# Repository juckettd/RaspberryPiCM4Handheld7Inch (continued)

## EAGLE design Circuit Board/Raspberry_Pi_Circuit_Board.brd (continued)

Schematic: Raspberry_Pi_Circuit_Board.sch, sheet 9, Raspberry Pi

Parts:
RPI_PINS1-100, RPI_PINS101-200: CONN-DF40_CL0594-5437-8-00_2D

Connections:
BITCLK_IN: RPI_PINS1-100.49; also elsewhere on the board
BT_REG_ON: RPI_PINS1-100.34; also elsewhere on the board
BT_UART_CTS: RPI_PINS1-100.29; also elsewhere on the board
BT_UART_RTS: RPI_PINS1-100.50; also elsewhere on the board
BT_UART_RXD: RPI_PINS1-100.51; also elsewhere on the board
BT_UART_TXD: RPI_PINS1-100.55; also elsewhere on the board
DATA_IN: RPI_PINS1-100.25; also elsewhere on the board
DSI1_C_N: RPI_PINS101-200.87; also elsewhere on the board
DSI1_C_P: RPI_PINS101-200.89; also elsewhere on the board
DSI1_D0_N: RPI_PINS101-200.75; also elsewhere on the board
DSI1_D0_P: RPI_PINS101-200.77; also elsewhere on the board
DSI1_D1_N: RPI_PINS101-200.81; also elsewhere on the board
DSI1_D1_P: RPI_PINS101-200.83; also elsewhere on the board
ETH0_N: RPI_PINS1-100.10; also elsewhere on the board
ETH0_P: RPI_PINS1-100.12; also elsewhere on the board
ETH1_N: RPI_PINS1-100.6; also elsewhere on the board
ETH1_P: RPI_PINS1-100.4; also elsewhere on the board
ETH2_N: RPI_PINS1-100.9; also elsewhere on the board
ETH2_P: RPI_PINS1-100.11; also elsewhere on the board
ETH3_N: RPI_PINS1-100.5; also elsewhere on the board
ETH3_P: RPI_PINS1-100.3; also elsewhere on the board
ETH_LEDG: RPI_PINS1-100.15; also elsewhere on the board
ETH_LEDY: RPI_PINS1-100.17; also elsewhere on the board
GLOBAL_EN: RPI_PINS1-100.99; also elsewhere on the board
GND: RPI_PINS1-100.1, RPI_PINS1-100.2, RPI_PINS1-100.7, RPI_PINS1-100.8, RPI_PINS1-100.13, RPI_PINS1-100.14, RPI_PINS1-100.22, RPI_PINS1-100.23, RPI_PINS1-100.32, RPI_PINS1-100.33, RPI_PINS1-100.42, RPI_PINS1-100.43, RPI_PINS1-100.52, RPI_PINS1-100.53, RPI_PINS1-100.59, RPI_PINS1-100.60, RPI_PINS1-100.65, RPI_PINS1-100.66, RPI_PINS1-100.71, RPI_PINS1-100.74, RPI_PINS1-100.98, RPI_PINS101-200.7, RPI_PINS101-200.8, RPI_PINS101-200.13, RPI_PINS101-200.14, RPI_PINS101-200.19, RPI_PINS101-200.20, RPI_PINS101-200.25, RPI_PINS101-200.26, RPI_PINS101-200.31, RPI_PINS101-200.32, RPI_PINS101-200.37, RPI_PINS101-200.38, RPI_PINS101-200.44, RPI_PINS101-200.50, RPI_PINS101-200.55, RPI_PINS101-200.56, RPI_PINS101-200.61, RPI_PINS101-200.62, RPI_PINS101-200.67, RPI_PINS101-200.68, RPI_PINS101-200.73, RPI_PINS101-200.74, RPI_PINS101-200.79, RPI_PINS101-200.80, RPI_PINS101-200.85, RPI_PINS101-200.86, RPI_PINS101-200.91, RPI_PINS101-200.92, RPI_PINS101-200.97, RPI_PINS101-200.98; also elsewhere on the board
GPIO7: RPI_PINS1-100.37; also elsewhere on the board
GPIO8: RPI_PINS1-100.39; also elsewhere on the board
GPIO9: RPI_PINS1-100.40; also elsewhere on the board
GPIO10: RPI_PINS1-100.44; also elsewhere on the board
GPIO11: RPI_PINS1-100.38; also elsewhere on the board
GPIO12: RPI_PINS1-100.31; also elsewhere on the board
HDMI0_CEC: RPI_PINS101-200.51; also elsewhere on the board
HDMI0_CK_N: RPI_PINS101-200.90; also elsewhere on the board
HDMI0_CK_P: RPI_PINS101-200.88; also elsewhere on the board
HDMI0_D0_N: RPI_PINS101-200.84; also elsewhere on the board
HDMI0_D0_P: RPI_PINS101-200.82; also elsewhere on the board
HDMI0_D1_N: RPI_PINS101-200.78; also elsewhere on the board
HDMI0_D1_P: RPI_PINS101-200.76; also elsewhere on the board
HDMI0_D2_N: RPI_PINS101-200.72; also elsewhere on the board
HDMI0_D2_P: RPI_PINS101-200.70; also elsewhere on the board
HDMI0_HOTPLUG: RPI_PINS101-200.53; also elsewhere on the board
HDMI0_SCL: RPI_PINS101-200.100; also elsewhere on the board
HDMI0_SDA: RPI_PINS101-200.99; also elsewhere on the board
NPWR_LED: RPI_PINS1-100.95; also elsewhere on the board
N_EXTRST: RPI_PINS1-100.100; also elsewhere on the board
N_RPIBOOT: RPI_PINS1-100.93; also elsewhere on the board
RP1.8: RPI_PINS1-100.78, RPI_PINS1-100.88, RPI_PINS1-100.90
RP3.3: RPI_PINS1-100.84, RPI_PINS1-100.86; also elsewhere on the board
RUN_PG: RPI_PINS1-100.92; also elsewhere on the board
SCL0: RPI_PINS1-100.80; also elsewhere on the board
SCL1: RPI_PINS1-100.56; also elsewhere on the board
SDA0: RPI_PINS1-100.82; also elsewhere on the board
SDA1: RPI_PINS1-100.58; also elsewhere on the board
SDIO_CLK: RPI_PINS1-100.46; also elsewhere on the board
SDIO_CMD: RPI_PINS1-100.47; also elsewhere on the board
SDIO_DATA0: RPI_PINS1-100.45; also elsewhere on the board
SDIO_DATA1: RPI_PINS1-100.41; also elsewhere on the board
SDIO_DATA2: RPI_PINS1-100.24; also elsewhere on the board
SDIO_DATA3: RPI_PINS1-100.48; also elsewhere on the board
SD_CLK: RPI_PINS1-100.57; also elsewhere on the board
SD_CMD: RPI_PINS1-100.62; also elsewhere on the board
SD_DAT0: RPI_PINS1-100.63; also elsewhere on the board
SD_DAT1: RPI_PINS1-100.67; also elsewhere on the board
SD_DAT2: RPI_PINS1-100.69; also elsewhere on the board
SD_DAT3: RPI_PINS1-100.61; also elsewhere on the board
SD_PWR_ON: RPI_PINS1-100.75; also elsewhere on the board
USB2_N: RPI_PINS101-200.3; also elsewhere on the board
USB2_P: RPI_PINS101-200.5; also elsewhere on the board
USBOTG: RPI_PINS101-200.1; also elsewhere on the board
VREF5.0: RPI_PINS1-100.77, RPI_PINS1-100.79, RPI_PINS1-100.81, RPI_PINS1-100.83, RPI_PINS1-100.85, RPI_PINS1-100.87; also elsewhere on the board
WL_REG_ON: RPI_PINS1-100.30; also elsewhere on the board
WORDSEL_IN: RPI_PINS1-100.26; also elsewhere on the board

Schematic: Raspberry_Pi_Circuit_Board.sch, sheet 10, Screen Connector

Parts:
LCD_CONN: FPC-1-84952-5

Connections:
DSI1_C_N: LCD_CONN.11; also elsewhere on the board
DSI1_C_P: LCD_CONN.10; also elsewhere on the board
DSI1_D0_N: LCD_CONN.8; also elsewhere on the board
DSI1_D0_P: LCD_CONN.7; also elsewhere on the board
DSI1_D1_N: LCD_CONN.14; also elsewhere on the board
DSI1_D1_P: LCD_CONN.13; also elsewhere on the board
GND: LCD_CONN.3, LCD_CONN.6, LCD_CONN.9, LCD_CONN.12, LCD_CONN.15, LCD_CONN.MP_1 (MP), LCD_CONN.MP_2 (MP); also elsewhere on the board
SCL0: LCD_CONN.5; also elsewhere on the board
SDA0: LCD_CONN.4; also elsewhere on the board
VREF3.3: LCD_CONN.1, LCD_CONN.2; also elsewhere on the board

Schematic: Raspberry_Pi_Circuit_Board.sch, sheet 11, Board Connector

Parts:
BOARD_CONN_1: MEZZANINE-AXT630124

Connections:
AGND: BOARD_CONN_1.11; also elsewhere on the board
AUDSD: BOARD_CONN_1.14; also elsewhere on the board
D+1: BOARD_CONN_1.10; also elsewhere on the board
D+2: BOARD_CONN_1.8; also elsewhere on the board
D-1: BOARD_CONN_1.9; also elsewhere on the board
D-2: BOARD_CONN_1.7; also elsewhere on the board
ETH0_N: BOARD_CONN_1.22; also elsewhere on the board
ETH0_P: BOARD_CONN_1.23; also elsewhere on the board
ETH1_N: BOARD_CONN_1.20; also elsewhere on the board
ETH1_P: BOARD_CONN_1.21; also elsewhere on the board
ETH2_N: BOARD_CONN_1.18; also elsewhere on the board
ETH2_P: BOARD_CONN_1.19; also elsewhere on the board
ETH3_N: BOARD_CONN_1.16; also elsewhere on the board
ETH3_P: BOARD_CONN_1.17; also elsewhere on the board
ETH_LEDG: BOARD_CONN_1.24; also elsewhere on the board
ETH_LEDY: BOARD_CONN_1.25; also elsewhere on the board
GND: BOARD_CONN_1.15, BOARD_CONN_1.26, BOARD_CONN_1.27, BOARD_CONN_1.28, BOARD_CONN_1.29, BOARD_CONN_1.30, BOARD_CONN_1.MP_1 (MP), BOARD_CONN_1.MP_2 (MP), BOARD_CONN_1.MP_3 (MP), BOARD_CONN_1.MP_4 (MP); also elsewhere on the board
OUTL: BOARD_CONN_1.12; also elsewhere on the board
OUTR: BOARD_CONN_1.13; also elsewhere on the board
VBUS1: BOARD_CONN_1.2, BOARD_CONN_1.3, BOARD_CONN_1.4, BOARD_CONN_1.5, BOARD_CONN_1.6; also elsewhere on the board
VREF3.3: BOARD_CONN_1.1; also elsewhere on the board

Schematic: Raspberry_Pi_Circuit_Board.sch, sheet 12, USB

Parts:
C1: 100uF; CAP-603
C18, C19, C20, C21: 10uF; CAP-603
C42, C43: 0.1uF; CAP-603
C52, C53: 27pF; CAP-603
CLK_24M: CLK-ECS-240
R23, R24: 2.2K; RES-603
R27: 12K; RES-603
R28: 15K; RES-603
R30, R31, R32, R33: 36K; RES-603
RPI_BOOT_SW: DIP-A6TN-1104
TP14, TP15: TESTPOINT
USB_CURLIM: CURLIM-AP22653W6
USB_HUB: USBPORT-USB2514BT-I/M2
USB_IN: USB-USB3131-30-0230-A
USB_POE: POE_PROT-TPD4EUSB30DQAR
USB_SWI: USB_SWITCH-FSUSB42-D

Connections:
D+1: USB_HUB.4; also elsewhere on the board
D+2: USB_HUB.7; also elsewhere on the board
D-1: USB_HUB.3; also elsewhere on the board
D-2: USB_HUB.6; also elsewhere on the board
GND: C1.A, C18.A, C19.A, C20.A, C21.A, C42.A, C43.A, C52.A, C53.A, CLK_24M.GND_1 (GND), CLK_24M.GND_2 (GND), R24.C, R27.C, R28.A, R30.C, R31.C, R32.C, R33.C, RPI_BOOT_SW.2, USB_CURLIM.GND, USB_HUB.37, USB_IN.GND, USB_IN.MP_1 (MP), USB_IN.MP_2 (MP), USB_POE.GND_1 (GND), USB_POE.GND_2 (GND), USB_SWI./OE, USB_SWI.GND; also elsewhere on the board
unnamed: R32.A, USB_HUB.28
unnamed: R28.C, USB_CURLIM.ILIM
unnamed: R31.A, USB_HUB.22
unnamed: R30.A, USB_HUB.24
unnamed: R23.A, TP15.TP, USB_IN.VBUS
unnamed: C53.C, CLK_24M.OUT/IN, USB_HUB.32
unnamed: C52.C, CLK_24M.IN/OUT, USB_HUB.33
unnamed: R33.A, USB_HUB.25
unnamed: R27.A, USB_HUB.35
N_EXTRST: USB_HUB.26; also elsewhere on the board
N_OCS1: USB_CURLIM.NFAULT, USB_HUB.13, USB_HUB.17, USB_HUB.19, USB_HUB.21
N_RPIBOOT: RPI_BOOT_SW.1; also elsewhere on the board
PWR1: USB_CURLIM.EN, USB_HUB.12
TD+: USB_HUB.2; also elsewhere on the board
TD-: USB_HUB.1; also elsewhere on the board
USB2_N: USB_SWI.D-; also elsewhere on the board
USB2_P: USB_SWI.D+; also elsewhere on the board
USBD_N: USB_IN.D+, USB_POE.D2+, USB_SWI.HSD2+
USBD_P: USB_IN.D-, USB_POE.D2-, USB_SWI.HSD2-
USBH_N: USB_HUB.30, USB_SWI.HSD1-
USBH_P: USB_HUB.31, USB_SWI.HSD1+
USBOTG: R23.C, R24.A, USB_SWI.SEL; also elsewhere on the board
VBUS1: C1.C, C21.C, TP14.TP, USB_CURLIM.OUT; also elsewhere on the board
VREF3.3: C18.C, C19.C, C42.C, C43.C, USB_HUB.5, USB_HUB.10, USB_HUB.15, USB_HUB.23, USB_HUB.27, USB_HUB.29, USB_HUB.36, USB_SWI.VCC; also elsewhere on the board
VREF5.0: C20.C, USB_CURLIM.IN; also elsewhere on the board

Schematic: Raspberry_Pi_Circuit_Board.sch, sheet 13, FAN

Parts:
C44: 0.1uF; CAP-603
D3: DIODE-X3-WLB1608-2
FAN_CONN: CONN-282834-2
R19: 10K; RES-603
TP16: TESTPOINT
TR3: TRAN-DMG2302UKQ

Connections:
GND: C44.A, R19.A, TR3.S; also elsewhere on the board
GPIO12: R19.C, TP16.TP, TR3.G; also elsewhere on the board
unnamed: D3.A, FAN_CONN.2, TR3.D
VREF3.3: C44.C, D3.C, FAN_CONN.1; also elsewhere on the board

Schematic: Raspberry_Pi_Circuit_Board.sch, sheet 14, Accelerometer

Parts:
ACCEL: MMA8451; MMA845X_QFN_16MM
C45: 0.1uF; CAP-603
R20: 10K; RES-603

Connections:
GND: ACCEL.5 (GND), ACCEL.10 (GND), ACCEL.12 (GND), C45.A; also elsewhere on the board
unnamed: ACCEL.2 (BYP), C45.C
SA0: ACCEL.7 (SA0), R20.A
SCL1: ACCEL.4 (SCL); also elsewhere on the board
SDA1: ACCEL.6 (SDA); also elsewhere on the board
VREF3.3: ACCEL.1 (VDDIO), ACCEL.14 (VDD), R20.C; also elsewhere on the board

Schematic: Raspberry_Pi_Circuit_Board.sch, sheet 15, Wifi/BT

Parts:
C61, C62: 0.1uF; CAP-603
C63, C64: 10uF; CAP-603
CLK-32.768: CLK-ECS-327
WIFI/BT: IC-LWB5+

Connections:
BT_REG_ON: WIFI/BT.32; also elsewhere on the board
BT_UART_CTS: WIFI/BT.46; also elsewhere on the board
BT_UART_RTS: WIFI/BT.44; also elsewhere on the board
BT_UART_RXD: WIFI/BT.43; also elsewhere on the board
BT_UART_TXD: WIFI/BT.45; also elsewhere on the board
GND: C61.A, C62.A, C63.A, C64.A, CLK-32.768.GND, WIFI/BT.1, WIFI/BT.8, WIFI/BT.14, WIFI/BT.16, WIFI/BT.27, WIFI/BT.28, WIFI/BT.29, WIFI/BT.35, WIFI/BT.42, WIFI/BT.48, WIFI/BT.49, WIFI/BT.51, WIFI/BT.G1 (GND), WIFI/BT.G2 (GND), WIFI/BT.G3 (GND), WIFI/BT.G4 (GND), WIFI/BT.G5 (GND), WIFI/BT.G6 (GND), WIFI/BT.G7 (GND), WIFI/BT.G8 (GND), WIFI/BT.G9 (GND), WIFI/BT.G10 (GND), WIFI/BT.G11 (GND), WIFI/BT.G12 (GND), WIFI/BT.G13 (GND), WIFI/BT.G14 (GND), WIFI/BT.G15 (GND), WIFI/BT.G16 (GND), WIFI/BT.G17 (GND); also elsewhere on the board
SDIO_CLK: WIFI/BT.15; also elsewhere on the board
SDIO_CMD: WIFI/BT.12; also elsewhere on the board
SDIO_DATA0: WIFI/BT.9; also elsewhere on the board
SDIO_DATA1: WIFI/BT.10; also elsewhere on the board
SDIO_DATA2: WIFI/BT.13; also elsewhere on the board
SDIO_DATA3: WIFI/BT.11; also elsewhere on the board
SUSCLK: CLK-32.768.OUT, WIFI/BT.34
VREF1.8: C61.C, C63.C, CLK-32.768.OE, CLK-32.768.VDD, WIFI/BT.4, WIFI/BT.5, WIFI/BT.30; also elsewhere on the board
VREF3.3: C62.C, C64.C, WIFI/BT.7, WIFI/BT.17, WIFI/BT.18; also elsewhere on the board
WL_REG_ON: WIFI/BT.33; also elsewhere on the board

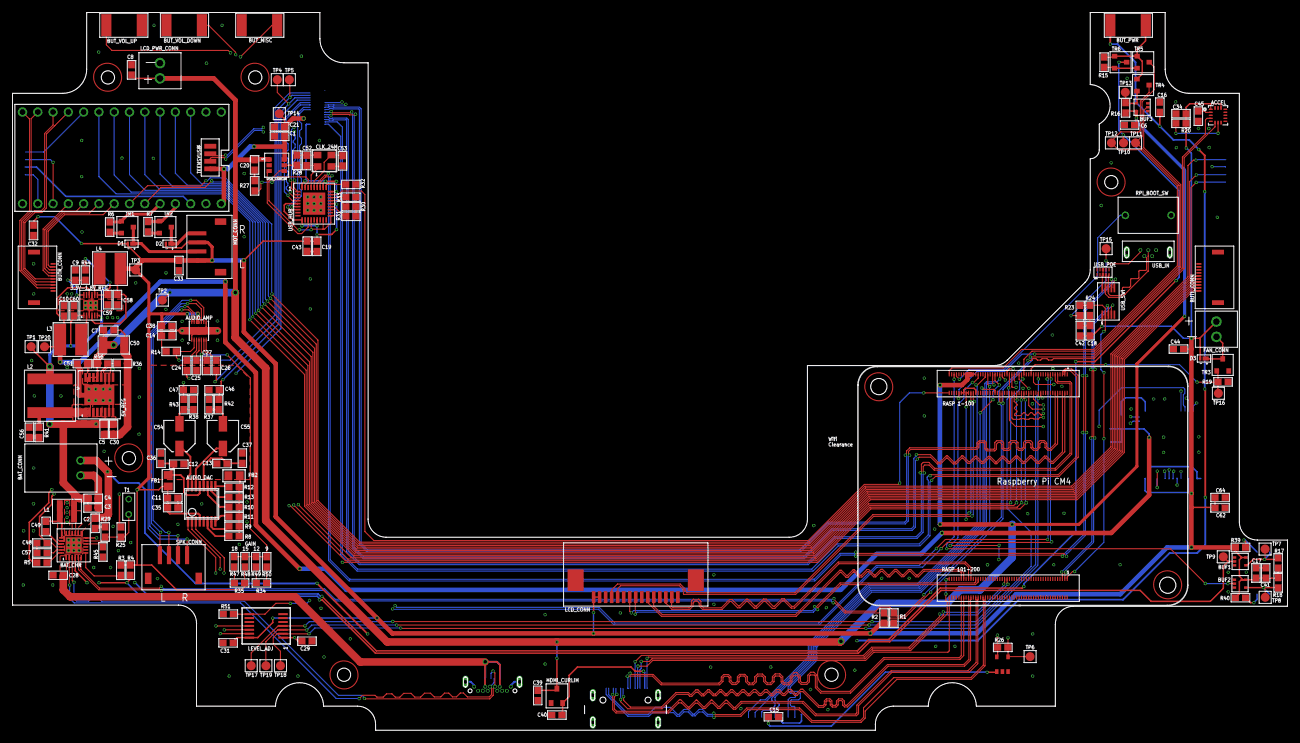
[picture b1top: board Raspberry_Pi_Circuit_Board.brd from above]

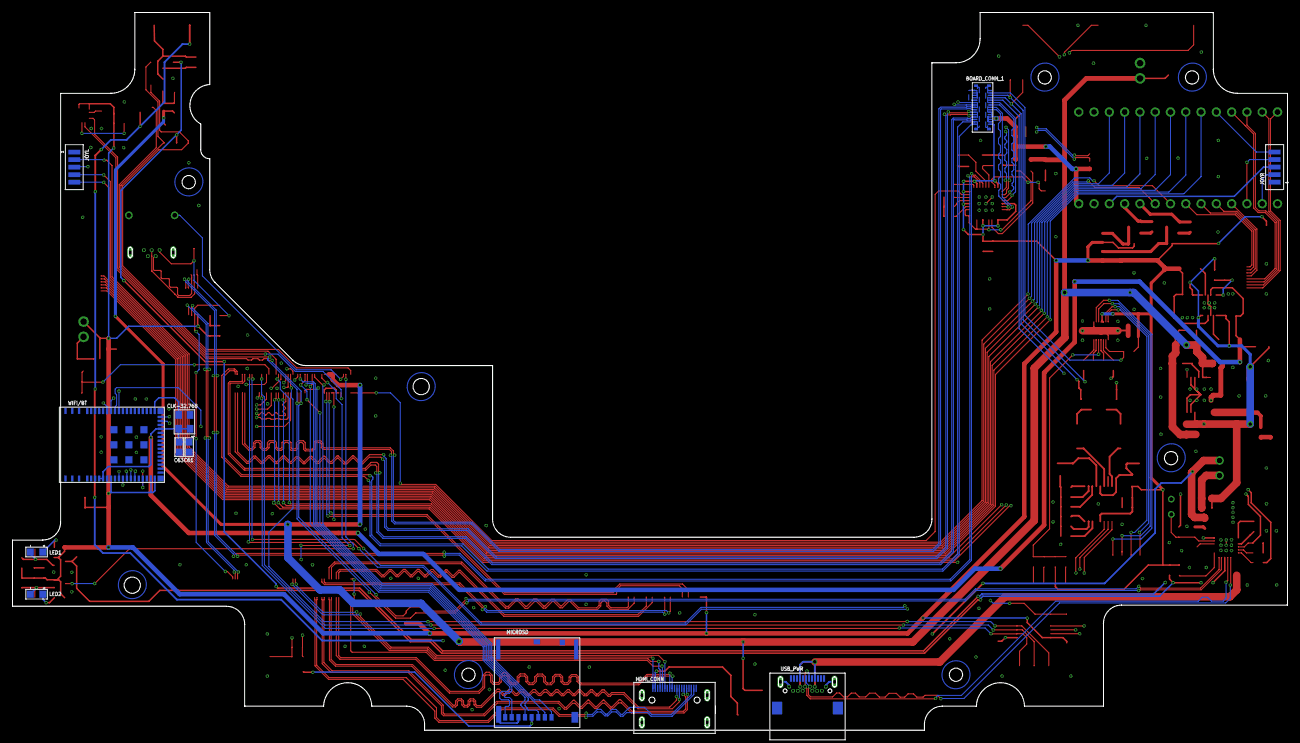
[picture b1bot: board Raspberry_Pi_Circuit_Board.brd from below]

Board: 4 copper layers, 211.9 x 119.3 mm, 192 parts (12 on the bottom side), 184 nets.

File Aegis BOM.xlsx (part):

Item | Component | Qty | Price | Total | Link
Power Items
Battery Charging IC | BAT_CHR | 1 | 3.76 | 3.76 | https://www.digikey.com/product-detail/en/texas-instruments/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
5V Boost IC | 5V_REG | 1 | 2.68 | 2.68 | https://www.digikey.com/en/products/detail/texas-instruments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
3.3V and 1.8V Buck IC | 3.3V-1.8V_REG | 1 | 0.76 | 0.76 | https://www.digikey.com/product-detail/en/diodes-incorporate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
2 pin Connection Header | BAT_CONN | 1 | 0.17 | 0.17 | https://www.digikey.com/product-detail/en/jst-sales-america-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
2 pin Connection Housing | BAT_PLUG | 1 | 0.1 | 0.1 | https://www.digikey.com/product-detail/en/jst-sales-america-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
Jumper Wires | BAT_WIRES | 1 | 0.76 | 0.76 | https://www.digikey.com/product-detail/en/jst-sales-america-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
USB-C Socket (PWR) | USB_PWR | 1 | 1.26 | 1.26 | https://www.digikey.com/en/products/detail/adam-tech/USB-C31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
Audio Items
UDA1334A | AUDIO_DAC | 1 | 0.25 | 0.25 | https://www.aliexpress.com/item/33049485687.html?spm=a2g0s.9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
MAX98306ETD+T | AUDIO_AMP | 1 | 1.91 | 1.91 | https://www.digikey.com/en/products/detail/maxim-integrated/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
Headphone Jack | AUDIO_PLUG | 1 | 1.38 | 1.38 | https://www.digikey.com/product-detail/en/adam-tech/ASJ-192-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
Audio Signal Level Adjust | LEVEL_ADJ | 1 | 0.92 | 0.92 | https://www.digikey.com/en/products/detail/texas-instruments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
USB Items
USB 2 Port Stacked | USB_CONN | 1 | 5.76 | 5.76 | https://www.digikey.com/en/products/detail/w%C3%BCrth-elektr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
USB Hub 4-port | USB_HUB | 1 | 3.05 | 3.05 | https://www.digikey.com/en/products/detail/microchip-technol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
USB Current Limit | USB_CURLIM | 1 | 0.42 | 0.42 | https://www.digikey.com/en/products/detail/diodes-incorporat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
24MHz Crystal | CLK_24M | 1 | 0.39 | 0.39 | https://www.digikey.com/en/products/detail/ecs-inc/ECS-240-9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
USB POE Protection | USB_POE | 1 | 0.79 | 0.79 | https://www.digikey.com/en/products/detail/texas-instruments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
USB Host/Slave Switch | USB_SWI | 1 | 0.6 | 0.6 | https://www.digikey.com/en/products/detail/on-semiconductor/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
USB Micro Input | USB_IN | 1 | 0.76 | 0.76 | https://www.digikey.com/en/products/detail/gct/USB3131-30-02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
RPI Boot Switch | RPI_BOOT_SW | 1 | 0.91 | 0.91 | https://www.digikey.com/en/products/detail/omron-electronics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
HDMI Items
HDMI Socket | HDMI_CONN | 1 | 1.73 | 1.73 | https://www.digikey.com/en/products/detail/cnc-tech/2001-1-2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
HDMI Current Limit | HDMI_CURLIM | 1 | 0.51 | 0.51 | https://www.digikey.com/en/products/detail/diodes-incorporat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
LCD Items
FPC Connector | LCD_CONN | 1 | 0.95 | 0.95 | https://www.digikey.com/en/products/detail/te-connectivity-a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
Micro SD Items
Micro SD Socket | MICROSD | 1 | 2.41 | 2.41 | https://www.digikey.com/product-detail/en/molex/5033981892/W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
Micro SD Power Switch | MICROSD_SWI | 1 | 1.52 | 1.52 | https://www.digikey.com/en/products/detail/richtek-usa-inc/R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
Ethernet
Ethernet Port | ETH_CONN | 1 | 8.2100000000000009 | 8.2100000000000009 | https://www.digikey.com/en/products/detail/kycon-inc/GLPLX-S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
Board Connectors
Mezzanine Connector (RP4) | RPI_PINR1-100, RPI_PINS101-200 | 2 | 1.73 | 3.46 | https://www.digikey.com/en/products/detail/hirose-electric-c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
Mezzanine Connector (Top Ports Board) | BOARD_CONN_2 | 1 | 1.36 | 1.36 | https://www.digikey.com/en/products/detail/panasonic-electri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
Mezzanine Header (Main Board) | BOARD_CONN_1 | 1 | 1.86 | 1.86 | https://www.digikey.com/en/products/detail/panasonic-electri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
Speaker/Motor Connector | SPK_CONN, MOT_CONN | 2 | 0.65 | 1.3 | https://www.digikey.com/en/products/detail/jst-sales-america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
Speaker/Motor Jumper | SPK_WIRE, MOT_WIRE | 2 | 1.79 | 3.58 | https://www.digikey.com/en/products/detail/jst-sales-america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
Fan Connector | FAN_CONN | 1 | 1.25 | 1.25 | https://www.digikey.com/en/products/detail/te-connectivity-a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
LCD Power Connector | LCD_PWR_CONN | 1 | 0.19 | 0.19 | https://www.digikey.com/en/products/detail/amphenol-icc-fci/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
Button Connector | BUTL_CONN, BUTR_CONN | 2 | 1.73 | 3.46 | https://www.digikey.com/product-detail/en/hirose-electric-co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
Buttons
Buttons | BUT_PWR, BUT_MISC, BUT_VOL_UP, BUT_VOL_DOWN | 4 | 0.65 | 2.6 | https://www.digikey.com/en/products/detail/c-k/KSS331GLFS/41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
LED
Amber LED | LED1, LED2 | 2 | 0.46 | 0.92 | https://www.digikey.com/en/products/detail/bivar-inc/SM0805A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
Buffer Component | BUF1, BUF2, BUF3 | 3 | 0.27 | 0.81 | https://www.digikey.com/en/products/detail/diodes-incorporat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
Accelerometer (Optional)
Accelerometer | ACCEL | 1 | 3.04 | 3.04 | https://www.digikey.com/en/products/detail/nxp-usa-inc/MMA84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
Wifi/Bluetooth (Optional)
Laird LWB5+ | WIFI/BT | 1 | 14.99 | 14.99 | https://www.digikey.com/en/products/detail/laird-connectivit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
Clock 32.768kHz | CLK_32.768K | 1 | 0.97 | 0.97 | https://www.digikey.com/en/products/detail/ecs-inc/ECS-327MV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
Transistors
Transistor NPN | TR1, TR2, TR3, TR4, TR5, TR6 | 6 | 0.42 | 2.52 | https://www.digikey.com/en/products/detail/diodes-incorporat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
Diodes
Diode 40V 2A | D1, D2, D3 | 3 | 0.41 | 1.23 | https://www.digikey.com/product-detail/en/diodes-incorporate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
Resistors
Res 10K (603) | R1, R2, R3, R4, R5, R6, R7, R8, R9, R10, R11, R12, R13, R14, R15, R16, R17, R18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 | 20 | 0.1 | 2 | https://www.digikey.com/product-detail/en/yageo/RC0603FR-071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
Res 1K (603) | R21, R22 | 2 | 0.13 | 0.26 | https://www.digikey.com/en/products/detail/vishay-beyschlag-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
Res 2.2K (603) | R23, R24, R39, R40 | 4 | 0.1 | 0.4 | https://www.digikey.com/en/products/detail/yageo/RC0603FR-07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
Res 5.23K (603) | R25 | 1 | 0.1 | 0.1 | https://www.digikey.com/product-detail/en/yageo/RC0603FR-075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
Res 12K (603) | R26, R27 | 2 | 0.1 | 0.2 | https://www.digikey.com/en/products/detail/yageo/RT0603DRE07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
Res 15K (603) | R28 | 1 | 0.1 | 0.1 | https://www.digikey.com/en/products/detail/yageo/RC0603FR-07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
Res 30.1K (603) | R29 | 1 | 0.33 | 0.33 | https://www.digikey.com/product-detail/en/yageo/RT0603BRD073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
Res 36K (603) | R30, R31, R32, R33 | 4 | 0.1 | 0.4 | https://www.digikey.com/en/products/detail/yageo/RC0603FR-07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
Res 50K (603) | R51 | 1 | 0.32 | 0.32 | https://www.digikey.com/en/products/detail/yageo/RT0603BRD07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
Res 100K (603) | R34, R35, R44 | 3 | 0.1 | 0.30000000000000004 | https://www.digikey.com/en/products/detail/yageo/RT0603DRE07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
Res 180K (603) | R36 | 1 | 0.1 | 0.1 | https://www.digikey.com/en/products/detail/yageo/RC0603FR-07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
Res 220K (603) | R37, R38 | 2 | 0.1 | 0.2 | https://www.digikey.com/en/products/detail/yageo/RC0603FR-07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
Res 47 (603) | R41 | 1 | 0.1 | 0.1 | https://www.digikey.com/en/products/detail/yageo/RT0603DRE07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
Res 100 (603) | R42, R43 | 2 | 0.17 | 0.34 | https://www.digikey.com/en/products/detail/yageo/RT0603DRD07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
Res 120 (603) | R45 | 1 | 0.1 | 0.1 | https://www.digikey.com/product-detail/en/yageo/RC0603FR-071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
Res 1.65M (603) | R46 | 1 | 0.1 | 0.1 | https://www.digikey.com/en/products/detail/yageo/RC0603FR-07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
Res 0 (603) | R47, R48, R49, R50 (1 for Gain) | 1 | 0.1 | 0.1 | https://www.digikey.com/en/products/detail/yageo/RC0603JR-07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
Capacitors
Cap 100uF (603) | C1 | 1 | 0.78 | 0.78 | https://www.digikey.com/en/products/detail/avx-corporation/F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
Cap 10uF (603) | C2, C3, C4, C5, C6, C7, C8, C9, C10, C11, C12, C13, C14, C15, C16, C17, C18, C1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 | 24 | 0.2 | 4.8000000000000007 | https://www.digikey.com/en/products/detail/murata-electronic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
Cap 1uF (603) | C24, C25, C26, C27, C28 | 5 | 0.25 | 1.25 | https://www.digikey.com/product-detail/en/murata-electronics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
Cap 0.1uF (603) | C29, C30, C31, C32, C33, C34, C35, C36, C37, C38, C39, C40, C41, C42, C43, C44,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 | 17 | 0.1 | 1.7000000000000002 | https://www.digikey.com/en/products/detail/samsung-electro-m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
Cap 0.01uF (603) | C46, C47 | 2 | 0.1 | 0.2 | https://www.digikey.com/en/products/detail/samsung-electro-m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
Cap 4.7uF (603) | C48, C59, C60 | 3 | 0.24 | 0.72 | https://www.digikey.com/product-detail/en/murata-electronics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
Cap 47nF (603) | C49 | 1 | 0.24 | 0.24 | https://www.digikey.com/product-detail/en/murata-electronics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
Cap 220uf (1411) | C50 | 1 | 1.2 | 1.2 | https://www.digikey.com/en/products/detail/vishay-sprague/T5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
Cap 2.2uF (603) | C51 | 1 | 0.13 | 0.13 | https://www.digikey.com/product-detail/en/kemet/C0603C225K4P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

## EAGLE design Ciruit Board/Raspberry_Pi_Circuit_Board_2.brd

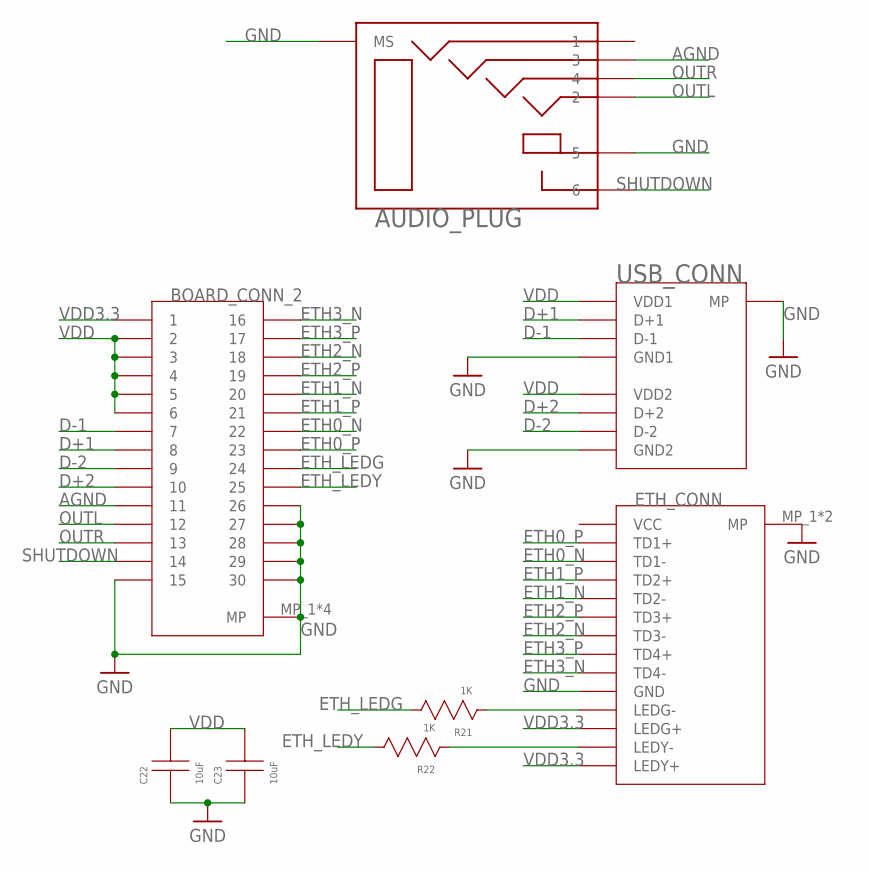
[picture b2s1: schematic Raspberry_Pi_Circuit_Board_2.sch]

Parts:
AUDIO_PLUG: AUDIOPLUG-ASJ-192-Y-TR
BOARD_CONN_2: MEZZANINE-AXT530124
C22, C23: 10uF; CAP-603
ETH_CONN: ETH-GLPLX-SMT-188S7-QQ-Y/G
R21, R22: 1K; RES-603
USB_CONN: USB-614108646521

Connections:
AGND: AUDIO_PLUG.3, BOARD_CONN_2.11
D+1: BOARD_CONN_2.8, USB_CONN.D+1
D+2: BOARD_CONN_2.10, USB_CONN.D+2
D-1: BOARD_CONN_2.7, USB_CONN.D-1
D-2: BOARD_CONN_2.9, USB_CONN.D-2
ETH0_N: BOARD_CONN_2.22, ETH_CONN.TD1-
ETH0_P: BOARD_CONN_2.23, ETH_CONN.TD1+
ETH1_N: BOARD_CONN_2.20, ETH_CONN.TD2-
ETH1_P: BOARD_CONN_2.21, ETH_CONN.TD2+
ETH2_N: BOARD_CONN_2.18, ETH_CONN.TD3-
ETH2_P: BOARD_CONN_2.19, ETH_CONN.TD3+
ETH3_N: BOARD_CONN_2.16, ETH_CONN.TD4-
ETH3_P: BOARD_CONN_2.17, ETH_CONN.TD4+
ETH_LEDG: BOARD_CONN_2.24, R21.C
ETH_LEDY: BOARD_CONN_2.25, R22.C
GND: AUDIO_PLUG.5, AUDIO_PLUG.MS1 (MS), AUDIO_PLUG.MS2 (MS), BOARD_CONN_2.15, BOARD_CONN_2.26, BOARD_CONN_2.27, BOARD_CONN_2.28, BOARD_CONN_2.29, BOARD_CONN_2.30, BOARD_CONN_2.MP_1 (MP), BOARD_CONN_2.MP_2 (MP), BOARD_CONN_2.MP_3 (MP), BOARD_CONN_2.MP_4 (MP), C22.A, C23.A, ETH_CONN.GND, ETH_CONN.MP_1 (MP), ETH_CONN.MP_2 (MP), USB_CONN.GND1, USB_CONN.GND2, USB_CONN.MP_1 (MP), USB_CONN.MP_2 (MP), USB_CONN.MP_3 (MP), USB_CONN.MP_4 (MP)
unnamed: ETH_CONN.LEDG-, R21.A
unnamed: ETH_CONN.LEDY-, R22.A
OUTL: AUDIO_PLUG.2, BOARD_CONN_2.12
OUTR: AUDIO_PLUG.4, BOARD_CONN_2.13
SHUTDOWN: AUDIO_PLUG.6, BOARD_CONN_2.14
VDD: BOARD_CONN_2.2, BOARD_CONN_2.3, BOARD_CONN_2.4, BOARD_CONN_2.5, BOARD_CONN_2.6, C22.C, C23.C, USB_CONN.VDD1, USB_CONN.VDD2
VDD3.3: BOARD_CONN_2.1, ETH_CONN.LEDG+, ETH_CONN.LEDY+

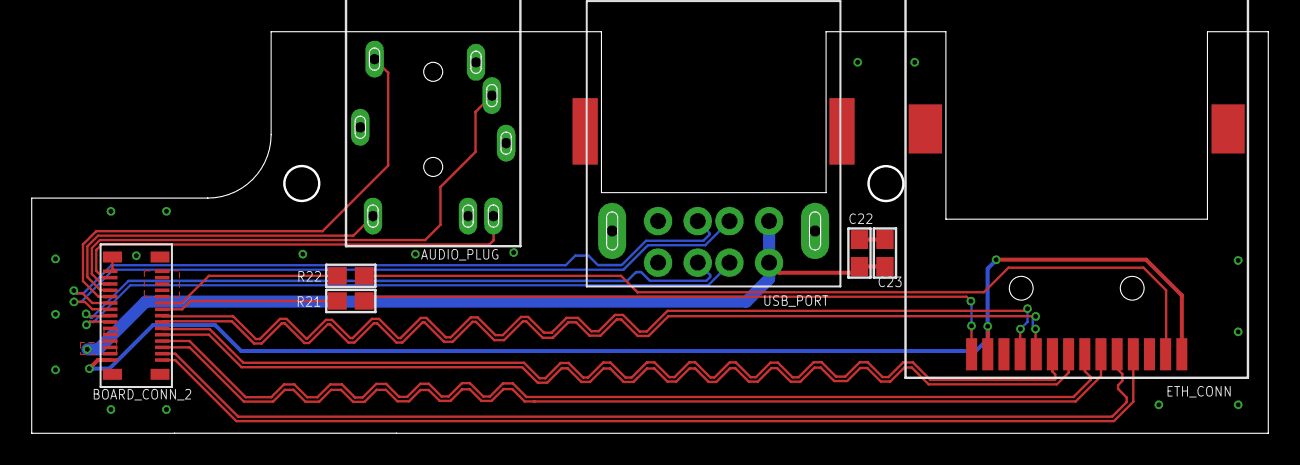
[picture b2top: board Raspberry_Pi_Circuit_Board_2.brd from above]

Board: 2 copper layers, 78.0 x 25.3 mm, 8 parts (0 on the bottom side), 23 nets.

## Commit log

2021-01-11 Update README.md
    Added initial description and the video links to youtube
2021-01-12 Add image to main README.
2021-01-12 Rename ReadMe to ReadMe.md
2021-01-12 Rename ReadMe.md to README.md
2021-03-03 Create LICENSE
2021-03-10 Adding all of the files for the first prototype to the repository
2021-03-10 Updating the Back.stl to the proper size
2021-03-10 Adding gerber files for the circuit boards
2021-03-10 renamed the ciruit board folder to "Circuit Board"
2021-04-17 Updating the following:
    Changed the folder structure so that I can keep track of the previous versions
    Added a change log
    Made various software updates to fix errors and improve functionality
2021-04-17 Update CHANGE_LOG.md
    Adding break lines to the change log
2021-04-17 Update CHANGE_LOG.md
    Updated the change log formatting
2021-04-17 Update CHANGE_LOG.md
    Updated the format of the change log again
2021-11-12 Added an fbx file for the case and updated some images
2021-11-12 Adding Fusion 360 Files of the case
2023-05-08 Adding the Version 2.0 with minor case and software changes. The Case changes are not required but make it more rigid for 3D Printing.
